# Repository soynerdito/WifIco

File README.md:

WifIco
=======

Small hardware adapter for ESP8266. Purpose make it 5v compatible and breadboard friendly.

Idea is to provide a small board to allow connecting the ESP8266 ver ESP02 to a breadboard. It is kept small so the price is cheap. A small batch was ordered to oshpark and waiting for order to arrive to see if the idea works.

**Features:**
- Allow input of 5V
- Exposes 3.3V regulated
- Level shifter for RX and TX signals (can be connected directly to Arduino)
- Breadboard friendly pinout
- Minu usb connector on the bottom (*for 5v power input only*)

For normal use please solder a wire on resistors R0XXX. This resistors are just exposing the RST and CHPD pins to allow moding the board for firmware updates.

Board design or prototype was NOT DONE! Just drawed a few versions on Eagle and order a batch of 3 boards to see what happens.
Plan is to scatter parts and build one and see what happens.

Blog post about project:
http://www.element14.com/community/groups/open-source-hardware/blog/2014/11/08/esp8266-interface-board-on-its-way

OSHPark board images

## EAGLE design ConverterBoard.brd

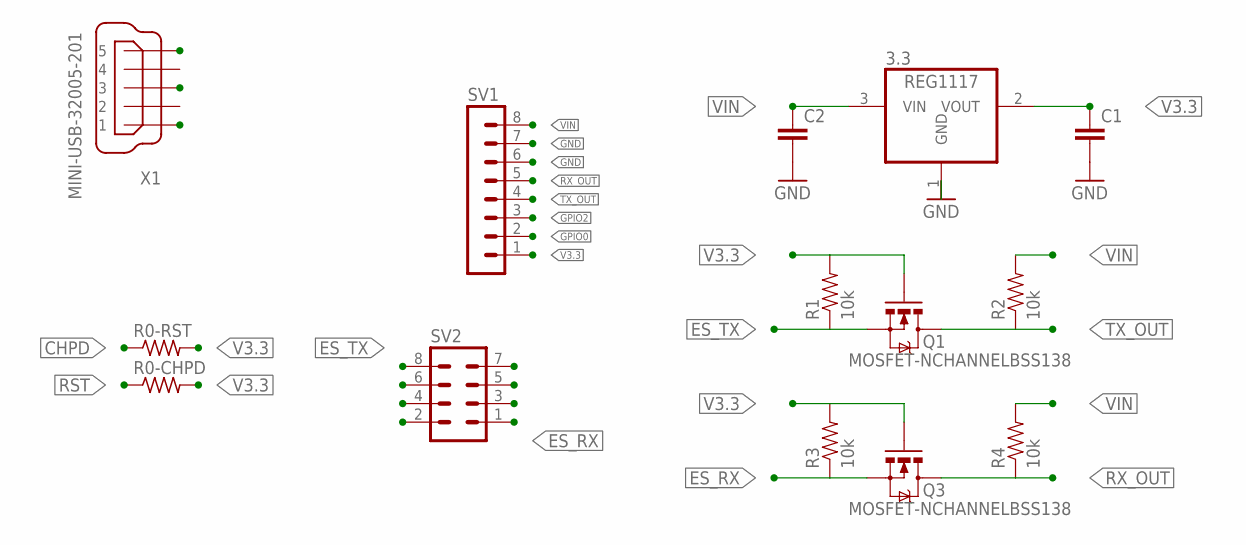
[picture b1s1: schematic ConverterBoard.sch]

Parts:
3.3: REG1117; SOT223
C1, C2: CC1808; C1808
Q1, Q3: MOSFET-NCHANNELBSS138; SOT23-3
R0-CHPD, R0-RST: R-US_R0603; R0603
R1, R2, R3, R4: 10k; 0805
SV1: MA08-1
SV2: MA04-2
X1: MINI-USB-32005-201; 32005-201

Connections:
CHPD: R0-RST.1, SV2.6
ES_RX: Q3.2 (S), R3.1, SV2.1
ES_TX: Q1.2 (S), R1.1, SV2.8
GND: 3.3.1 (GND), C1.2, C2.2, SV1.6, SV1.7, SV2.7, X1.5
GPIO0: SV1.2, SV2.3
GPIO2: SV1.3, SV2.5
RST: R0-CHPD.1, SV2.4
RX_OUT: Q3.3 (D), R4.1, SV1.5
TX_OUT: Q1.3 (D), R2.1, SV1.4
V3.3: 3.3.2 (VOUT), C1.1, Q1.1 (G), Q3.1 (G), R0-CHPD.2, R0-RST.2, R1.2, R3.2, SV1.1, SV2.2
VIN: 3.3.3 (VIN), C2.1, R2.2, R4.2, SV1.8, X1.1

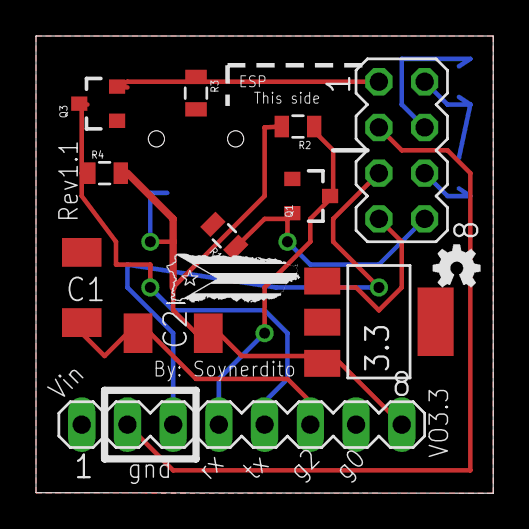
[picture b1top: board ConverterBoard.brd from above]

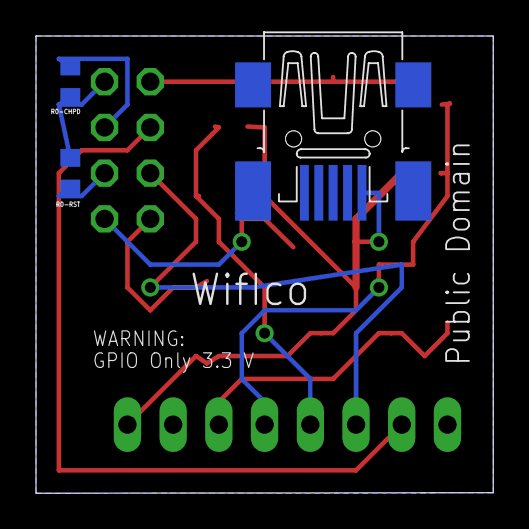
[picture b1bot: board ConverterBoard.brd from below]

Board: 2 copper layers, 25.4 x 25.4 mm, 14 parts (3 on the bottom side), 11 nets.

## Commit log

2014-11-08 Initial update
2014-11-08 Adding OSHPark board images
2014-11-08 Added link to blog post

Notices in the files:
ConverterBoard.brd:
Public Domain
parts and their libraries:
SparkFun-DiscreteSemi: Licensing: Creative Commons ShareAlike 4.0 International - https://creativecommons.org/licenses/by-sa/4.0
